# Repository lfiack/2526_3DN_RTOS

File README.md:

# 2526 3DN

## Systèmes à microcontrôleurs
* Les TD de Systèmes à microcontrôleurs sont disponibles ici : [mcu/td/README.md](mcu/td/README.md)
* Les TP de Systèmes à microcontrôleurs sont disponibles ici : [mcu/tp/README.md](mcu/tp/README.md)

## Noyau temps-réel

* Le projet STM32CubeIDE vu en cours est disponible dans le dossier [rtos/cours_rtos](rtos/cours_rtos/).
* Les corrigés de TD sont disponibles dans le dossier [rtos/td](rtos/td/) :
1. TD1 : [rtos/td/td1.md](rtos/td/td1.md)
2. TD2 : [rtos/td/td2.md](rtos/td/td2.md)
3. TD3 : [rtos/td/td3.md](rtos/td/td3.md)

## Linux embarqué
* Les TP de Linux embarqué sont disponibles ici : 
1. [linux/tp1.md](linux/tp1.md)
2. [linux/tp2.md](linux/tp2.md)
3. [linux/tp3.md](linux/tp3.md)

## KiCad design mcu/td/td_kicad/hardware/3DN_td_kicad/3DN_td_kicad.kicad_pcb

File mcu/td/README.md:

# 3DN TD KiCAD
## Objectifs

Concevoir un projet simple sur KiCAD autour d'un STM32.

Liste des AAV :
1. Lister les composants nécessaires au STM32 pour fonctionner,
2. Concevoir un schéma propre, sans erreurs, lisible et maintenable,
3. Décrire les règles de placement des composants : Connecteurs, HMI, faciliter le routage,
4. Configurer les contraintes du logiciel en fonction des règles du fabricant (DFM pour Design for Manufacturability), 
5. Router un circuit en appliquant un ensemble de règles pour éviter les problèmes de CEM (Compatibilité Électro-Magnétique),
6. Générer les fichiers de fabrication.

## Création du projet

Deux logiciels à utiliser simultanément : 
* STM32CubeMX
* KiCAD

1. Lancez-les. 
2. Créez un dossier de travail qui contiendra les projets des deux logiciels. 
**Attention**, le dossier ne doit contenir ni espaces ni accents. 
2. **Dans STM32CubeMX**, créez un projet pour le MCU **STM32G031K8Tx**. Nommez-le à votre convenance, sans espace, sans accent.
3. Quels éléments sont nécessaires pour faire fonctionner le STM32 ?
4. **Dans KiCAD**, créez un projet. Nommez-le à votre convenance, sans espace, sans accent.
5. Configurez le cartouche.

## Configuration du STM32

De retour dans **STM32CubeMX**.

1. Activez le mode debug. _Lockez_ les pins correspondantes.

> SYS > Serial Wire

2. Repérez la pin reset (```NRST```) et _lockez_-la.
3. Activez l'**USART1**. 
Notez que pour certains périphériques les pins peuvent être déplacées :

> Ctrl + Clic gauche

Nommez les pins ```VCP_RX``` et ```VCP_TX``` respectivement sur ```PB7``` et ```PB6```.

4. Que signifie ```VCP``` ?

C'est tout ce que nous avons besoin pour faire démarrer un STM32. Ajoutons quelques périphériques, pour le sport:

5. Activez les channels **IN0** et **IN1** de l'**ADC1**.
6. Activez le **SPI1**. Pensez à activer le **Hardware NSS**, et expliquez ce que ça signifie.
7. Activez l'**I2C2**.
8. Activez les _channels_ 3 et 4 en mode **PWM Generation** de **TIM3**. Nommez-les LED1 et LED2.
9. Pourquoi utiliser une sortie de _timer_ pour une LED ?
10. Tentez de regrouper les pins au mieux et _lockez_-les.

## Tracé du schéma

Le logiciel dispose de beaucoup raccourcis claviers utiles. Commencez à les apprendre dès maintenant.

1. Ajoutez les composants principaux :
    * ```STM32G031K8Tx```, renommez-le en ```STM32G031K8T6```,
    * ```Conn_ST_STDC14```, choisissez la bonne empreinte,
    * ```MIC5504-3.3YM5```.
2. Quels sont leurs rôles ?
3. Ajoutez les **connecteurs** suivants de la librairie ```Connector_Generic```. Choisissez une empreinte de type ```JST-XH```. Renommez-les.
    * Un connecteur 4 broches pour l'**ADC**,
    * Un connecteur 4 broches pour l'**I2C**,
    * Un connecteur 6 broches pour le **SPI**.
4. Selon la _datasheet_ du ```MIC5504-3.3YM5```, quels composants doit-on ajouter ? Ajoutez-les. Tous les composants passifs seront de taille ```0603```.
5. Même question pour le ```STM32G031K8T6```.
6. En utilisant des _labels_ si nécessaire, connectez le connecteur de la **STLink** au **STM32**.
7. Connectez les **ADC**, l'**I2C** et le **SPI** aux connecteurs correspondants.
8. Pourquoi l'**I2C** a besoin de résistances de _pull-up_ ? Ajoutez-les. Configurez-les en _Do not populate_.
9. Ajoutez une LED témoin sur le ```+3V3``` et les deux LED de _status_ sur les sorties du _timer_.
10. Ajoutez 4 trous de fixation : ```MountingHole_3.2mm_M3_Pad_Via``` et reliez-les à la masse.
11. Indiquez les pins non-utilisées avec le ```No Connect Flag```.
12. Passez un peu de temps à organiser et à documenter votre schéma.
13. Vérifiez et corrigez les erreurs avec le ```Electrical Rules Checker```.

## Configuration de l'outil de routage

Même si ce n'est pas nécessaire dans cet exercice, vous allez concevoir un **PCB 4 couches**.
Les couches internes seront dédiées à la **masse** et aux **alimentations**.

Ce PCB ne sera pas fabriqué, mais ceux du TP le seront, alors prenez les bonnes habitudes.
Les PCB de TP seront fabriqués par la société [JLCPCB](https://jlcpcb.com/).

1. Sur le site de [JLCPCB](https://jlcpcb.com/), notez les capacités du fabricant en terme d'**isolation**, de **largeur de pistes** et de **taille de via**.
2. Reportez ces informations dans KiCAD (_Board Setup_). Configurez le PCB en 4 couches.
3. Pour des raisons de CEM, ce n'est pas toujours une bonne idée d'utiliser les pistes les plus fines possibles.
Ajoutez les _Pre-defined Sizes_ suivantes :
    * ```Track``` ```Width``` : **0.3mm**
    * ```Track``` ```Width``` : **0.4mm**
    * ```Track``` ```Width``` : **0.5mm**
    * ```Vias``` ```Diameter``` : **0.5mm** ; ```Hole``` : **0.3mm**
4. Configurez la ```Net Class``` ```Default``` à **0.3mm** avec les bonnes valeurs de _Clearance_ et de taille de _Via_.
5. Configurez la grille à 1mm. Vous allez passer votre temps à changer la taille de grille, c'est normal.
6. Configurez le cartouche.
7. ```Update PCB from Schematic```. Il ne devrait pas y en avoir d'erreurs, sinon il faudra les corriger dans le schéma.

## Placement des composants

1. Commencez par placer les trous de fixation selon un carré de **40mm** par **40mm**.
2. Tracez les ```Edge Cuts```.
3. Placez le **STM32** au milieu.
4. Placez les connecteurs sur les côtés.
5. Essayez au maximum de réduire les croisements dans le **chevelu** (_ratsnest_ en anglais).
6. Plus vous passerez de temps sur cette étape, moins vous passerez de temps sur le routage. 
N'hésitez pas à multiplier les allez-retours avec le schéma et **STM32CubeMX** pour réduire les croisements.
7. Allez voir la vue 3D.

## Routage

1. Tracez un _Filled Zone_ sur la couche **In1.Cu** connecté au signal ```GND```.
2. Tracez un _Filled Zone_ sur la couche **In2.Cu** connecté au signal ```+3V3```.
3. Sur la même couche **In2.Cu**, tracez un _Fill Zone_ de ```+5V``` pour relier le connecteur à l'entrée du **LDO**.
4. Reliez tous les ```+5V```, ```+3V3``` et ```GND``` aux différents plans à l'aide de vias.
5. Routez le reste des signaux.
6. Ajouter un plan de masse sur les couches **Top** et **Bottom**.
7. Retirez les antennes parasites. Ajoutez des _stitching vias_.
8. Vérifiez qu'il n'y ait pas d'erreurs dans _Design Rule Checker_.

## Finitions

1. Organisez proprement la sérigraphie.
2. Ajoutez toutes les informations qui vous semble nécessaire sur la sérigraphie.
3. Ajoutez un logo.
4. Vérifiez dans la vue 3D.
5. Revérifiez les DRC. On sait jamais.

## Fichiers de fabrication

1. Générez les fichers de fabrication GERBER ainsi que les fichiers de perçage.
2. Faites une simulation de commande sur le site [JLCPCB](https://jlcpcb.com/).

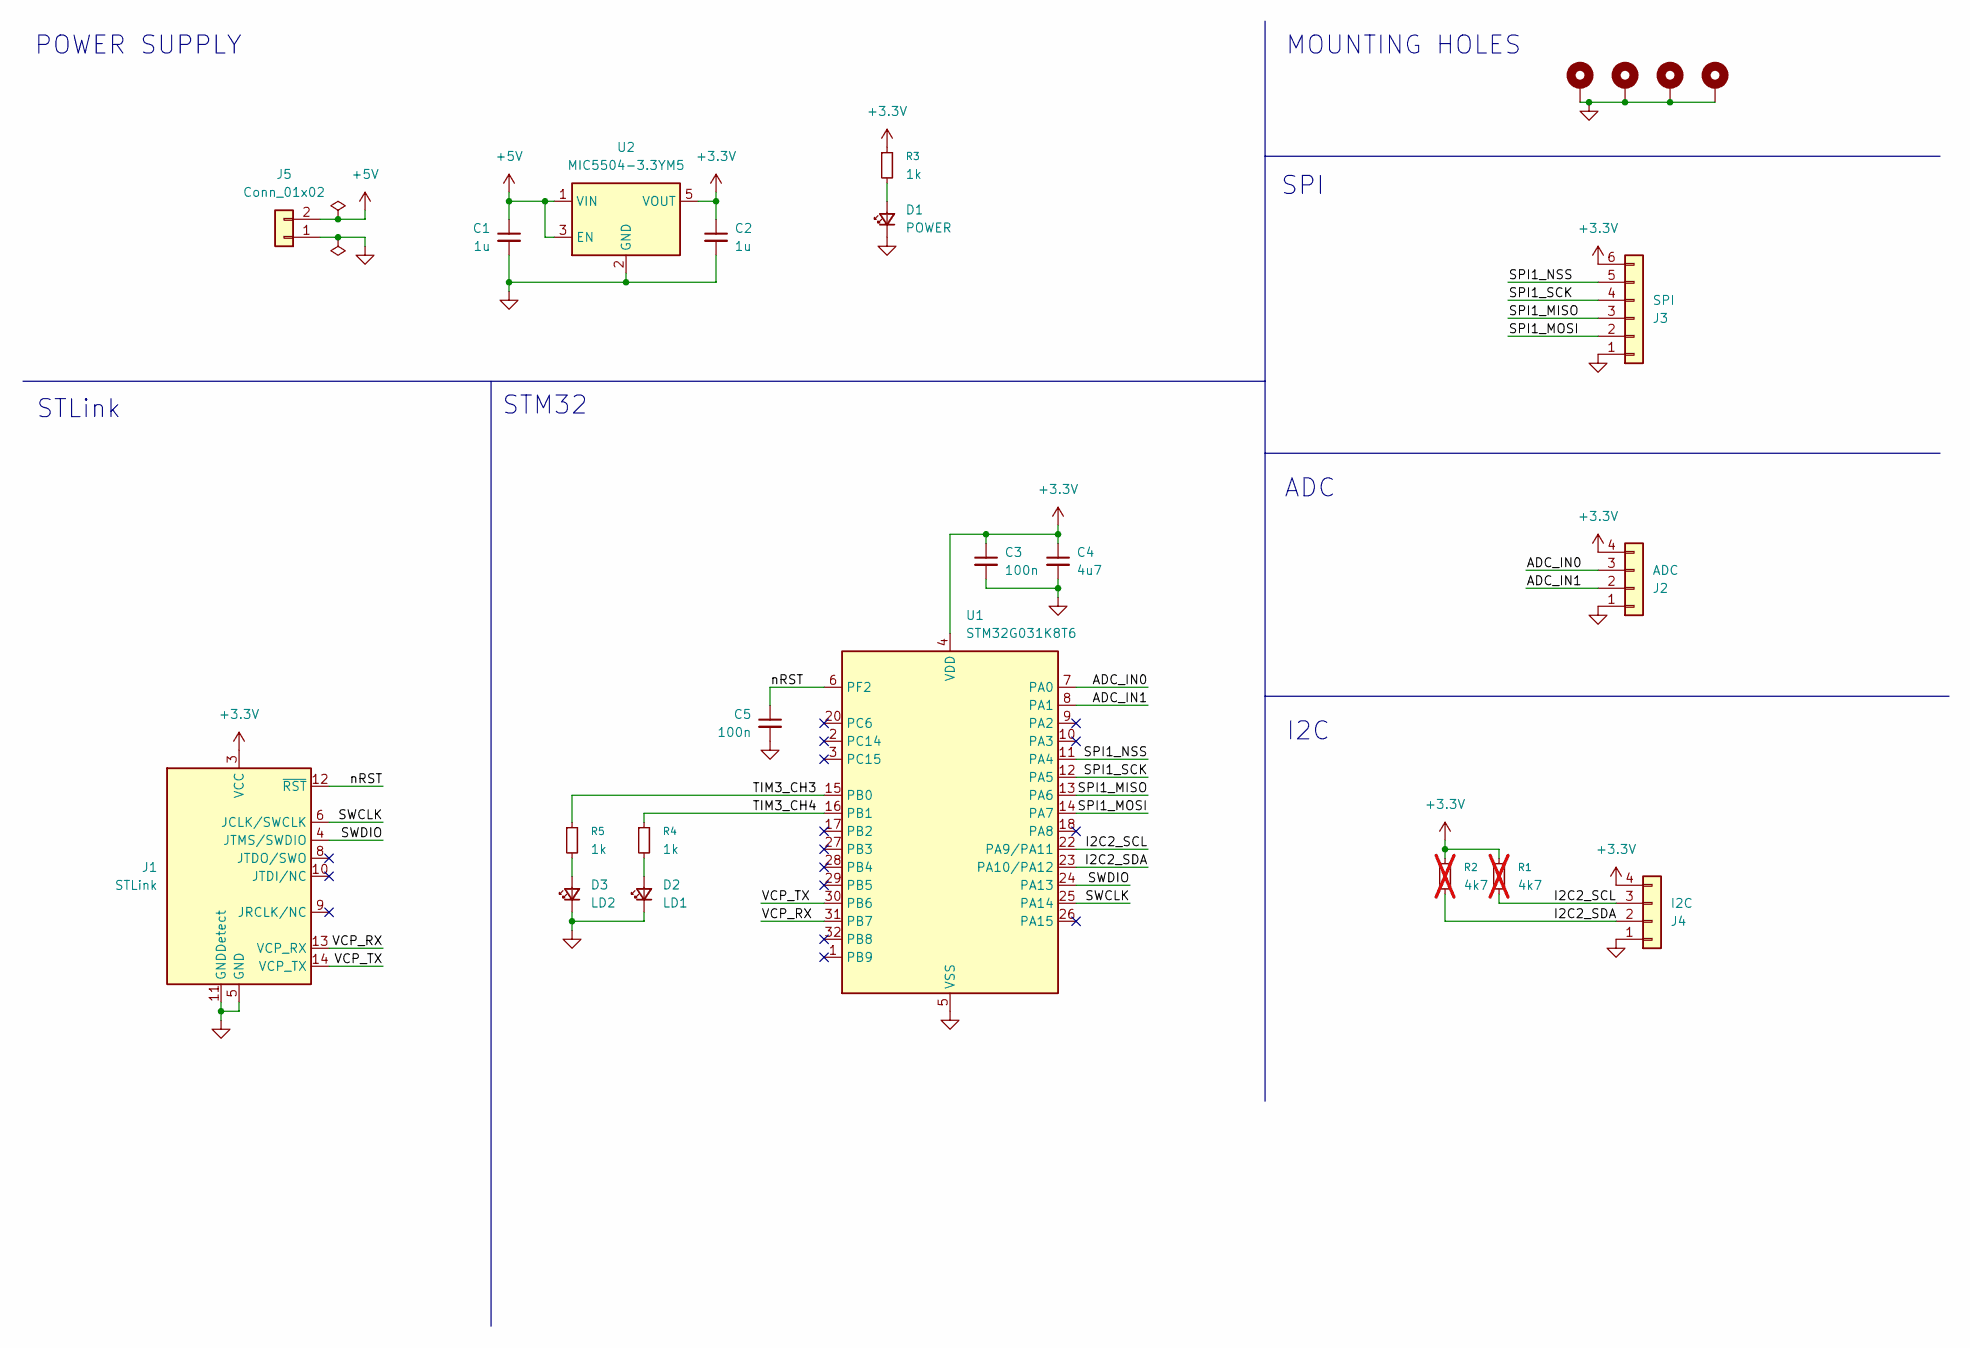
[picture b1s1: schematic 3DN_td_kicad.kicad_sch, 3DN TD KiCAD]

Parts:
C1, C2: 1u; C_0603_1608Metric_Pad1.08x0.95mm_HandSolder
C3, C5: 100n; C_0603_1608Metric_Pad1.08x0.95mm_HandSolder
C4: 4u7; C_0603_1608Metric_Pad1.08x0.95mm_HandSolder
D1: POWER; LED_0603_1608Metric_Pad1.05x0.95mm_HandSolder
D2: LD1; LED_0603_1608Metric_Pad1.05x0.95mm_HandSolder
D3: LD2; LED_0603_1608Metric_Pad1.05x0.95mm_HandSolder
H1, H2, H3, H4: MountingHole_Pad; MountingHole_3.2mm_M3_Pad_Via
J1: STLink; PinHeader_2x07_P1.27mm_Vertical_SMD
J2: ADC; JST_XH_B4B-XH-A_1x04_P2.50mm_Vertical
J3: SPI; JST_XH_B6B-XH-A_1x06_P2.50mm_Vertical
J4: I2C; JST_XH_B4B-XH-A_1x04_P2.50mm_Vertical
J5: Conn_01x02; JST_XH_B2B-XH-A_1x02_P2.50mm_Vertical
R1, R2: 4k7; R_0603_1608Metric_Pad0.98x0.95mm_HandSolder; not fitted
R3, R4, R5: 1k; R_0603_1608Metric_Pad0.98x0.95mm_HandSolder
U1: STM32G031K8T6; LQFP-32_7x7mm_P0.8mm
U2: MIC5504-3.3YM5; SOT-23-5_HandSoldering

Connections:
+3.3V: C2.1, C3.1, C4.1, J1.3 (VCC), J2.4, J3.6, J4.4, R1.1, R2.1, R3.1, U1.4 (VDD), U2.5 (VOUT)
+5V: C1.1, J5.2, U2.1 (VIN), U2.3 (EN)
/ADC_IN0: J2.3, U1.7 (PA0)
/ADC_IN1: J2.2, U1.8 (PA1)
/I2C2_SCL: J4.3, R1.2, U1.22 (PA9/PA11)
/I2C2_SDA: J4.2, R2.2, U1.23 (PA10/PA12)
/SPI1_MISO: J3.3, U1.13 (PA6)
/SPI1_MOSI: J3.2, U1.14 (PA7)
/SPI1_NSS: J3.5, U1.11 (PA4)
/SPI1_SCK: J3.4, U1.12 (PA5)
/SWCLK: J1.6 (JCLK/SWCLK), U1.25 (PA14)
/SWDIO: J1.4 (JTMS/SWDIO), U1.24 (PA13)
/TIM3_CH3: R5.1, U1.15 (PB0)
/TIM3_CH4: R4.1, U1.16 (PB1)
/VCP_RX: J1.13 (VCP_RX), U1.31 (PB7)
/VCP_TX: J1.14 (VCP_TX), U1.30 (PB6)
/nRST: C5.1, J1.12 (~RST), U1.6 (PF2)
GND: C1.2, C2.2, C3.2, C4.2, C5.2, D1.1 (K), D2.1 (K), D3.1 (K), H1.1, H2.1, H3.1, H4.1, J1.5 (GND), J1.7 (GND), J1.11 (GNDDetect), J2.1, J3.1, J4.1, J5.1, U1.5 (VSS), U2.2 (GND)
unnamed: D1.2 (A), R3.2
unnamed: D2.2 (A), R4.2
unnamed: D3.2 (A), R5.2

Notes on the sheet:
I2C
STM32
STLink
ADC
SPI
MOUNTING HOLES
POWER SUPPLY

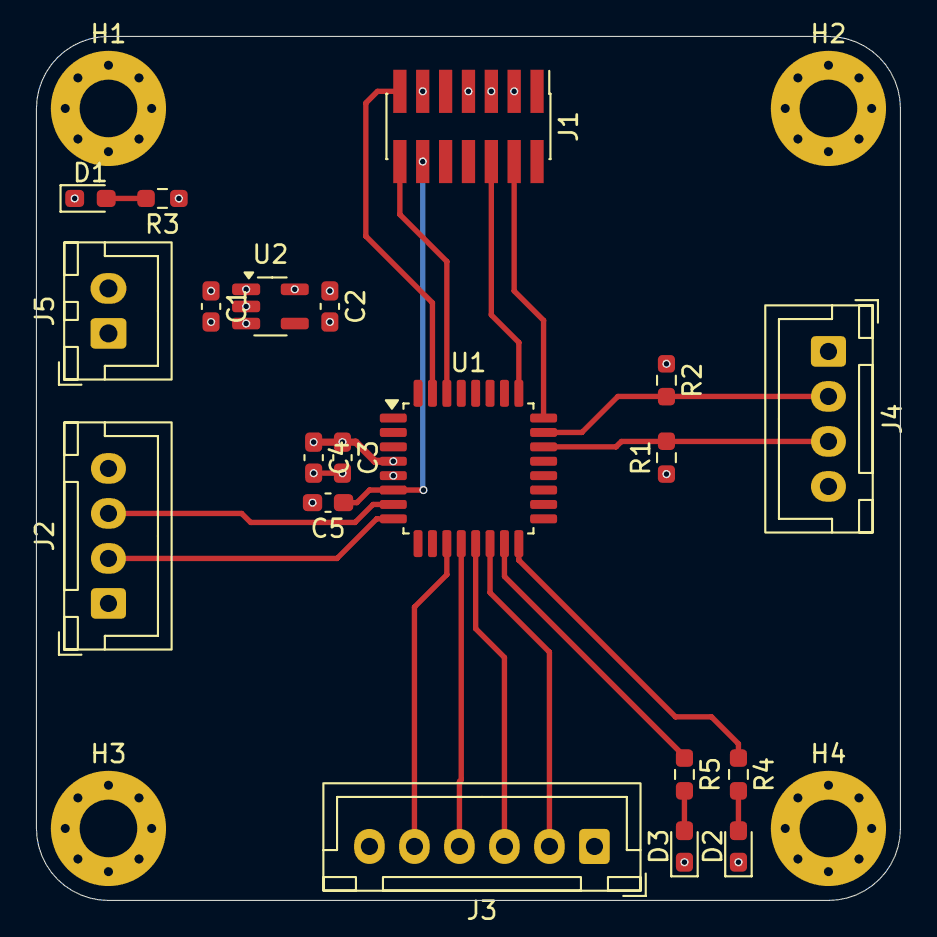
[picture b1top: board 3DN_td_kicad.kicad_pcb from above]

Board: 4 copper layers, 48.0 x 48.0 mm, 24 parts (0 on the bottom side), 21 nets.

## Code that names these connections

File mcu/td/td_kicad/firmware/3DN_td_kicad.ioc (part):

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Mcu.Name=STM32G031K(4-6-8)Tx
Mcu.Package=LQFP32
Mcu.UserName=STM32G031K8Tx
PA0.Mode=IN0
PA0.Signal=ADC1_IN0
PA1.Mode=IN1
PA1.Signal=ADC1_IN1
PA11\ [PA9].Mode=I2C
PA11\ [PA9].Signal=I2C2_SCL
PA12\ [PA10].Mode=I2C
PA12\ [PA10].Signal=I2C2_SDA
PA13.Mode=Serial_Wire
PA13.Signal=SYS_SWDIO
PA14-BOOT0.Mode=Serial_Wire
PA14-BOOT0.Signal=SYS_SWCLK
PA4.Mode=NSS_Signal_Hard_Output
PA4.Signal=SPI1_NSS
PA5.Mode=Full_Duplex_Master
PA5.Signal=SPI1_SCK
PA6.Mode=Full_Duplex_Master
PA6.Signal=SPI1_MISO
PA7.Mode=Full_Duplex_Master
PA7.Signal=SPI1_MOSI
PB0.Signal=S_TIM3_CH3
PB1.Signal=S_TIM3_CH4
PB6.GPIOParameters=GPIO_Label
PB6.GPIO_Label=VCP_TX
PB6.Mode=Asynchronous
PB6.Signal=USART1_TX
PB7.GPIOParameters=GPIO_Label
PB7.GPIO_Label=VCP_RX
PB7.Mode=Asynchronous
PB7.Signal=USART1_RX
RCC.HSE_VALUE=8000000
RCC.SYSCLKFreq_VALUE=16000000
board=custom

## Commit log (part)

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2026-01-28 fin cours 1
2026-01-30 cours 2
2026-02-04 TD système à MCU
2026-02-06 TD kicad schematics
2026-02-06 cours RTOS notifications
2026-02-11 added documentation to schematic
2026-02-11 routing
2026-02-11 Sujet TP Systèmes à microcontrôleurs
2026-02-11 readme
2026-02-11 typos
2026-02-11 organisation dossier rtos
2026-02-11 correction RTOS TD2
2026-02-11 Typo
2026-02-11 Correction RTOS TD3
2026-03-09 td shell
2026-03-09 td queue
2026-03-09 addition
2026-03-09 Shell with FreeRTOS
2026-03-10 uart irq + semaphore
2026-05-27 TP Linux embarqué
